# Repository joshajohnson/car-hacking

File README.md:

# Car Hacking

A repo for assorted tools, projects, and documentation.

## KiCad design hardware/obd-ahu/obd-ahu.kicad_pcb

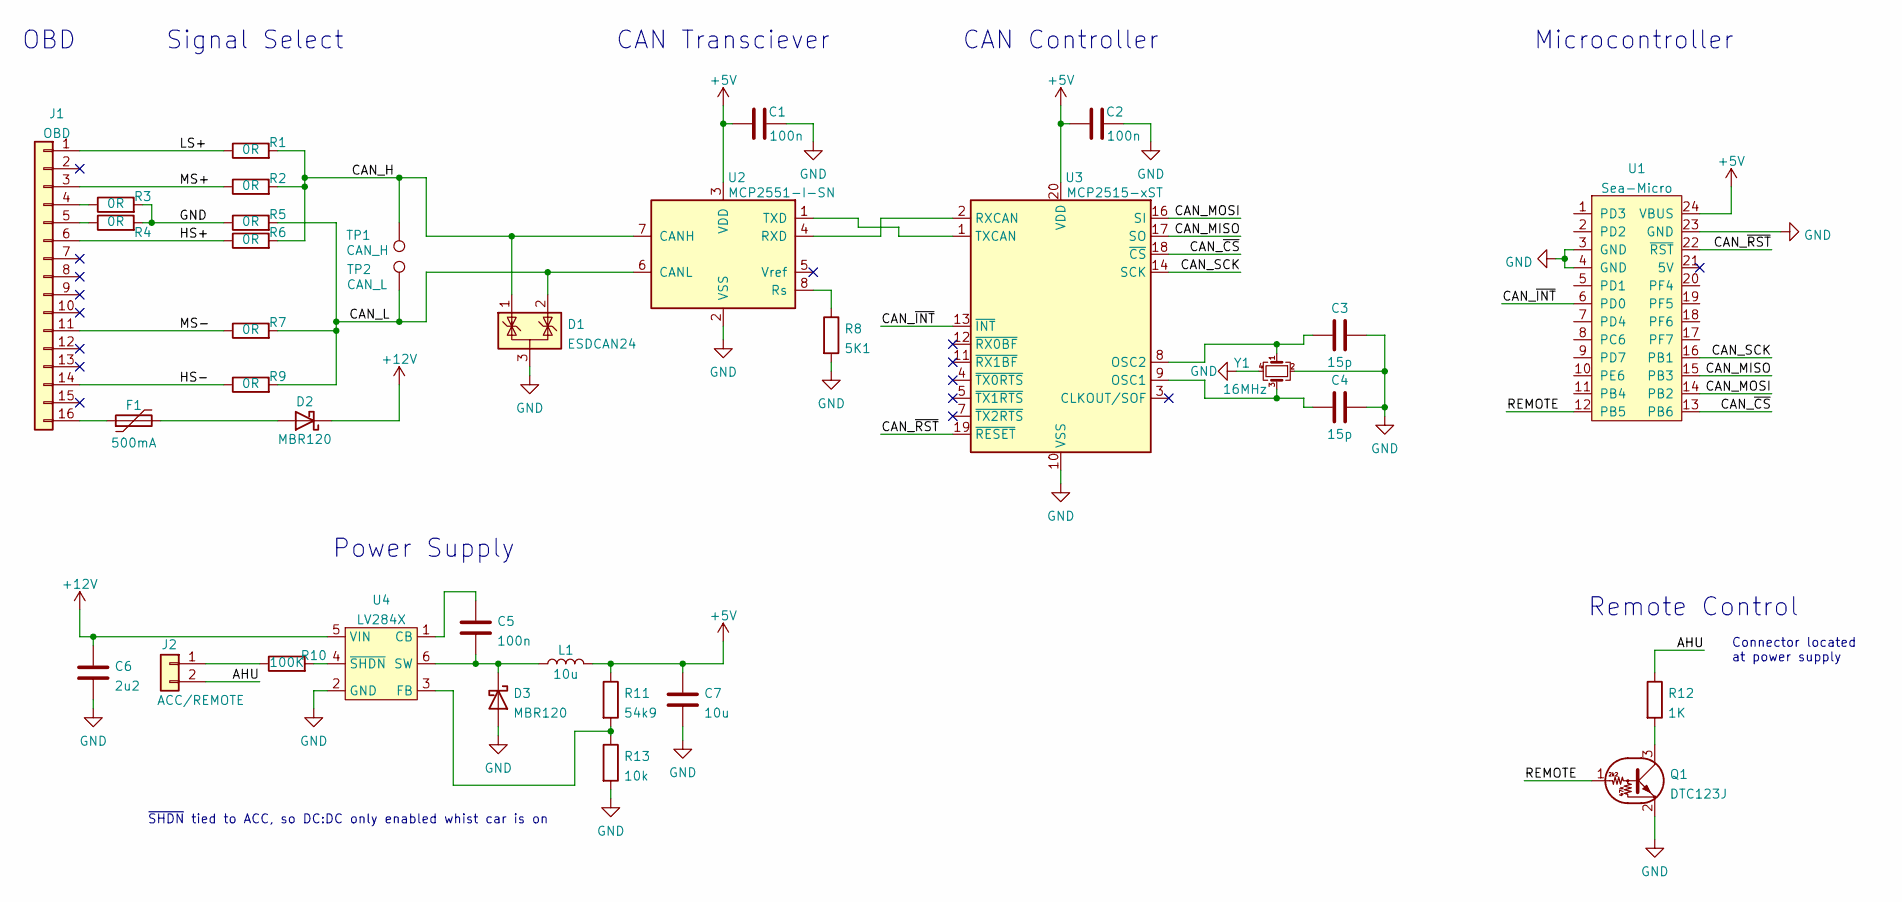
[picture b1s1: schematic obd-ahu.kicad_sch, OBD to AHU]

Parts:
C1, C2, C5: 100n; C_0603_1608Metric
C3, C4: 15p; C_0603_1608Metric; MPN CL10C150JB8NNNC; LCSC C1644
C6: 2u2; C_0805_2012Metric
C7: 10u; C_0805_2012Metric
D1: ESDCAN24; SOT-23
D2, D3: MBR120; D_SOD-123FL
F1: 500mA; Fuse_0805_2012Metric
J1: OBD; OBD-II-Sparkfun
J2: ACC/REMOTE; TerminalBlock_4Ucon_1x02_P3.50mm_Horizontal
L1: 10u; L_1210_3225Metric
Q1: DTC123J; TSOT-23
R1, R2, R5, R6, R7, R9: 0R; R_0603_1608Metric
R3, R4: 0R; R_0805_2012Metric
R8: 5K1; R_0603_1608Metric
R10: 100K; R_0603_1608Metric
R11: 54k9; R_0603_1608Metric
R12: 1K; R_0603_1608Metric
R13: 10k; R_0603_1608Metric
TP1: CAN_H; TestPoint_THTPad_D1.5mm_Drill0.7mm
TP2: CAN_L; TestPoint_THTPad_D1.5mm_Drill0.7mm
U1: Sea-Micro; Arduino_Pro_Micro
U2: MCP2551-I-SN; SOIC-8_3.9x4.9mm_P1.27mm
U3: MCP2515-xST; TSSOP-20_4.4x6.5mm_P0.65mm
U4: LV284X; TSOT-23-6
Y1: 16MHz; Crystal_SMD_3225-4Pin_3.2x2.5mm; MPN TAXM16M4RDBCCT2T; LCSC C164044

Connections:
+5V: C1.1, C2.1, C7.1, L1.2, R11.1, U1.24 (VBUS), U2.3 (VDD), U3.20 (VDD)
+12V: C6.1, D2.1 (K), U4.5 (VIN)
/AHU: J2.2, R12.1
/CAN_H: D1.1 (K), R1.2, R2.2, R6.2, TP1.1, U2.7 (CANH)
/CAN_L: D1.2 (K), R5.2, R7.2, R9.2, TP2.1, U2.6 (CANL)
/CAN_MISO: U1.15 (PB3), U3.17 (SO)
/CAN_MOSI: U1.14 (PB2), U3.16 (SI)
/CAN_SCK: U1.16 (PB1), U3.14 (SCK)
/CAN_~CS: U1.13 (PB6), U3.18 (~CS)
/CAN_~INT: U1.6 (PD0), U3.13 (~INT)
/CAN_~RST: U1.22 (~RST), U3.19 (~RESET)
/HS+: J1.6, R6.1
/HS-: J1.14, R9.1
/LS+: J1.1, R1.1
/MS+: J1.3, R2.1
/MS-: J1.11, R7.1
/REMOTE: Q1.1 (B), U1.12 (PB5)
GND: C1.2, C2.2, C3.2, C4.2, C6.2, C7.2, D1.3 (A), D3.2 (A), Q1.2 (E), R3.2, R4.2, R5.1, R8.2, R13.2, U1.3 (GND), U1.4 (GND), U1.23 (GND), U2.2 (VSS), U3.10 (VSS), U4.2 (GND), Y1.2, Y1.4
unnamed: C3.1, U3.8 (OSC2), Y1.1
unnamed: C4.1, U3.9 (OSC1), Y1.3
unnamed: C5.1, U4.1 (CB)
unnamed: C5.2, D3.1 (K), L1.1, U4.6 (SW)
unnamed: D2.2 (A), F1.2
unnamed: F1.1, J1.16
unnamed: J1.4, R3.1
unnamed: J1.5, R4.1
unnamed: Q1.3 (C), R12.2
unnamed: R8.1, U2.8 (Rs)
unnamed: J2.1, R10.1
unnamed: R10.2, U4.4 (~SHDN)
unnamed: R11.2, R13.1, U4.3 (FB)
unnamed: U2.1 (TXD), U3.1 (TXCAN)
unnamed: U2.4 (RXD), U3.2 (RXCAN)

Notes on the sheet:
OBD
~{SHDN} tied to ACC, so DC:DC only enabled whist car is on
Signal Select
Power Supply
CAN Transciever
CAN Controller
Microcontroller
Remote Control
Connector located at power supply

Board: 2 copper layers, 35 parts (35 on the bottom side), 33 nets, no tracks yet.

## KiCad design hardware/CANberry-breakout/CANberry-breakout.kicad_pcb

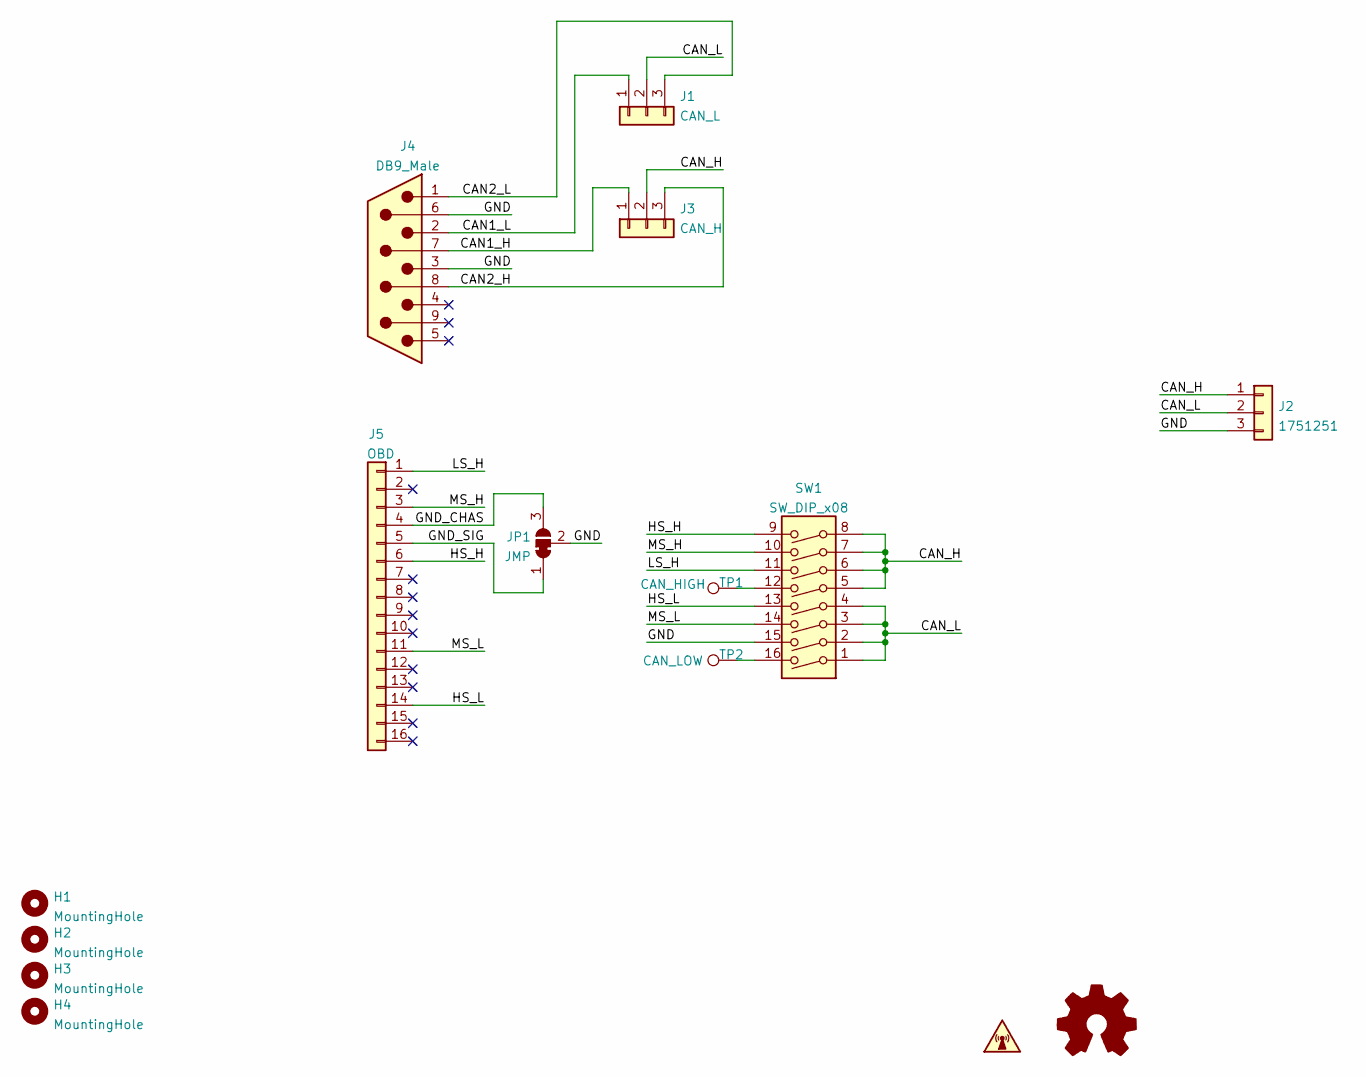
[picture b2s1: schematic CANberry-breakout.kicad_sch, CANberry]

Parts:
H1, H2, H3, H4: MountingHole; MountingHole_3.2mm_M3
J1: CAN_L; 3_PIN_THT_Staggered
J2: 1751251; TerminalBlock_393570003_1x03_P3.50mm_Horizontal; MPN 1751251; LCSC C91152
J3: CAN_H; 3_PIN_THT_Staggered
J4: DB9_Male; DSUB-9_Male_Horizontal_P2.77x2.84mm_EdgePinOffset7.70mm_Hou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
J5: OBD; OBD-II-Sparkfun
JP1: JMP; SolderJumper-3_P1.3mm_Bridged12_RoundedPad1.0x1.5mm
LOGO1: Logo_Open_Hardware_Small; OSHW-Symbol_8.9x8mm_Copper
SW1: SW_DIP_x08; SW_DIP_SPSTx08_Slide_9.78x22.5mm_W7.62mm_P2.54mm
SYM1: Canberry
TP1: CAN_HIGH; TestPoint_THTPad_D2.0mm_Drill1.0mm
TP2: CAN_LOW; TestPoint_THTPad_D2.0mm_Drill1.0mm

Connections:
/CAN1_H: J3.1, J4.7
/CAN1_L: J1.1, J4.2
/CAN2_H: J3.3, J4.8
/CAN2_L: J1.3, J4.1
/CAN_H: J2.1, J3.2, SW1.5, SW1.6, SW1.7, SW1.8
/CAN_L: J1.2, J2.2, SW1.1, SW1.2, SW1.3, SW1.4
/GND: J2.3, J4.3, J4.6, JP1.2 (C), SW1.15
/GND_CHAS: J5.4, JP1.3 (B)
/GND_SIG: J5.5, JP1.1 (A)
/HS_H: J5.6, SW1.9
/HS_L: J5.14, SW1.13
/LS_H: J5.1, SW1.11
/MS_H: J5.3, SW1.10
/MS_L: J5.11, SW1.14
unnamed: SW1.12, TP1.1
unnamed: SW1.16, TP2.1

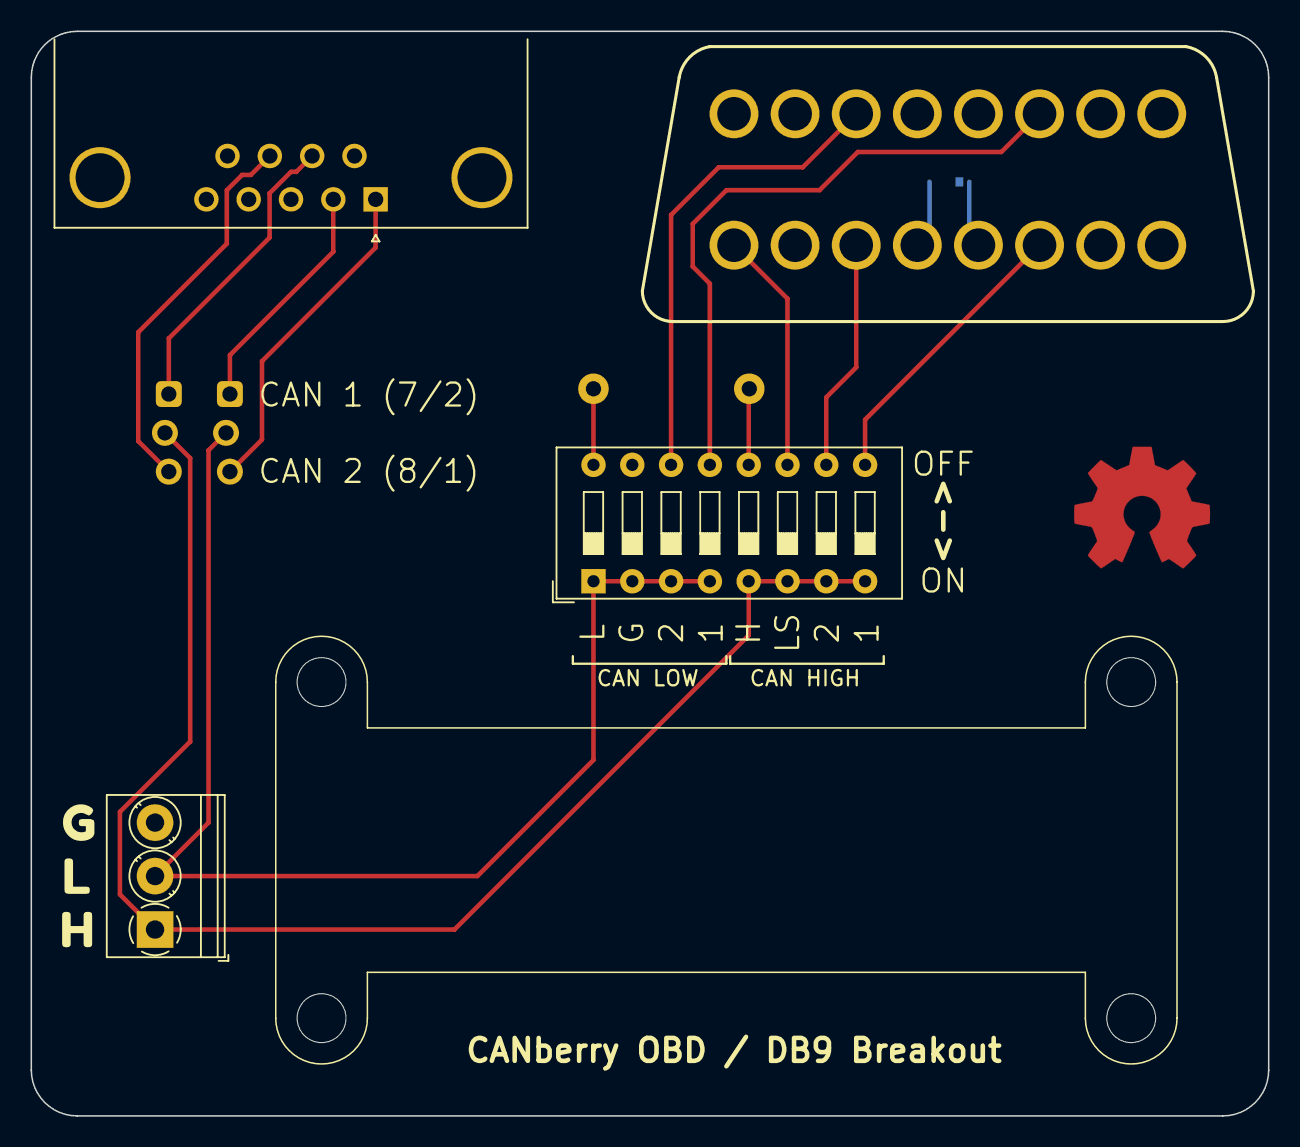
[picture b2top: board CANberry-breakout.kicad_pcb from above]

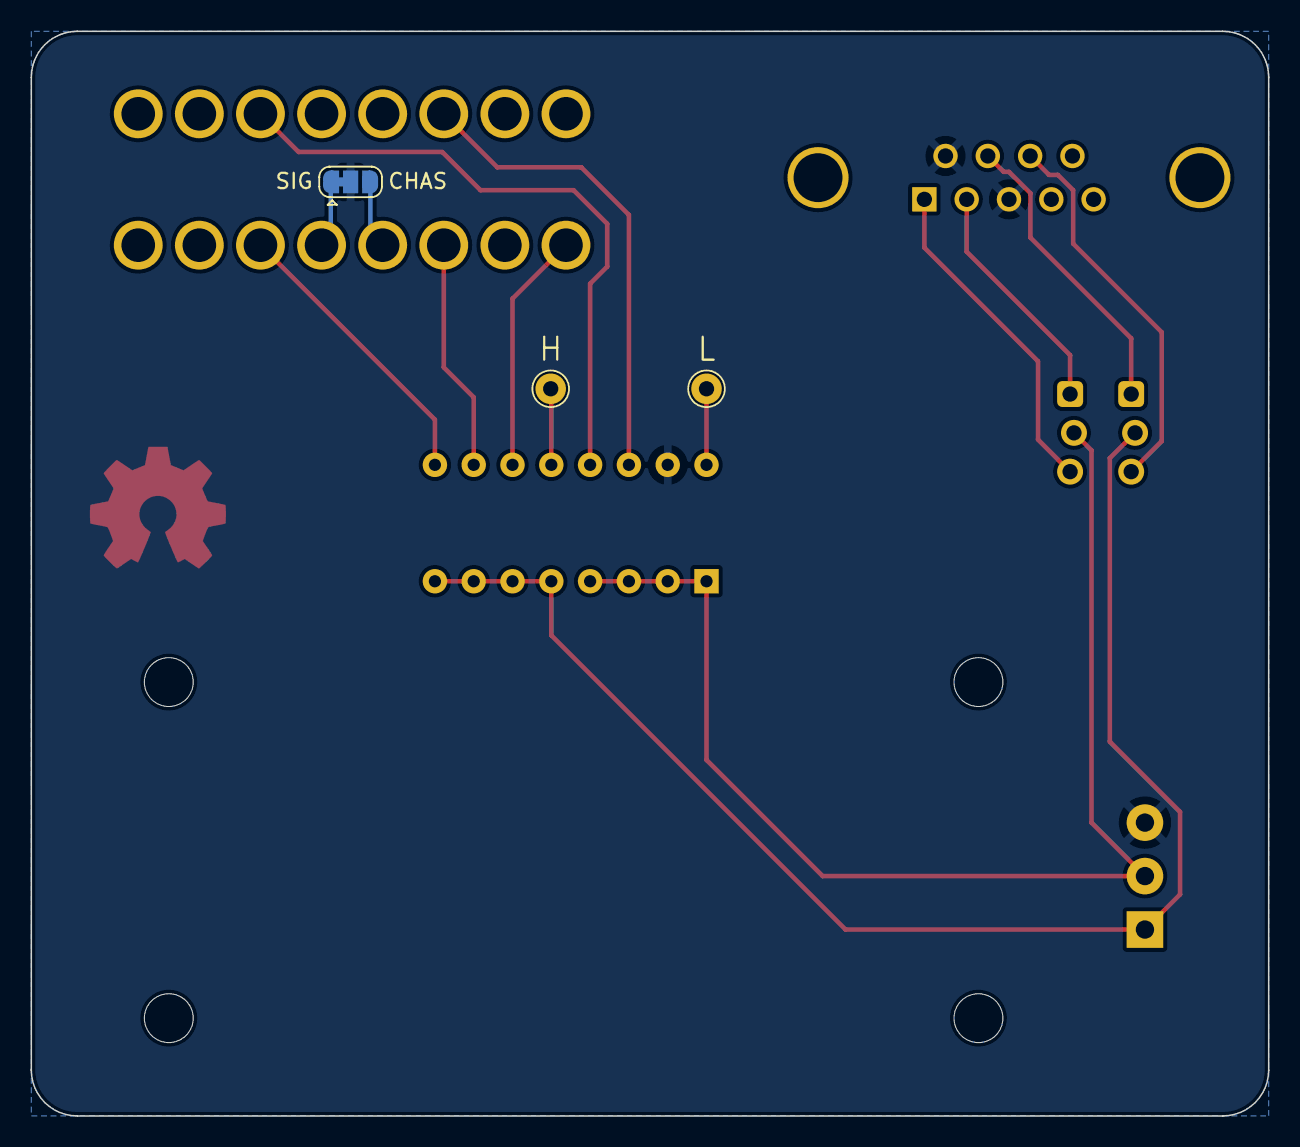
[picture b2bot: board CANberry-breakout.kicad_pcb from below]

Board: 2 copper layers, 81.0 x 71.0 mm, 18 parts (3 on the bottom side), 16 nets.

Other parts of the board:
svg2mod, svg2mod#2, svg2mod#3: G***; svg2mod

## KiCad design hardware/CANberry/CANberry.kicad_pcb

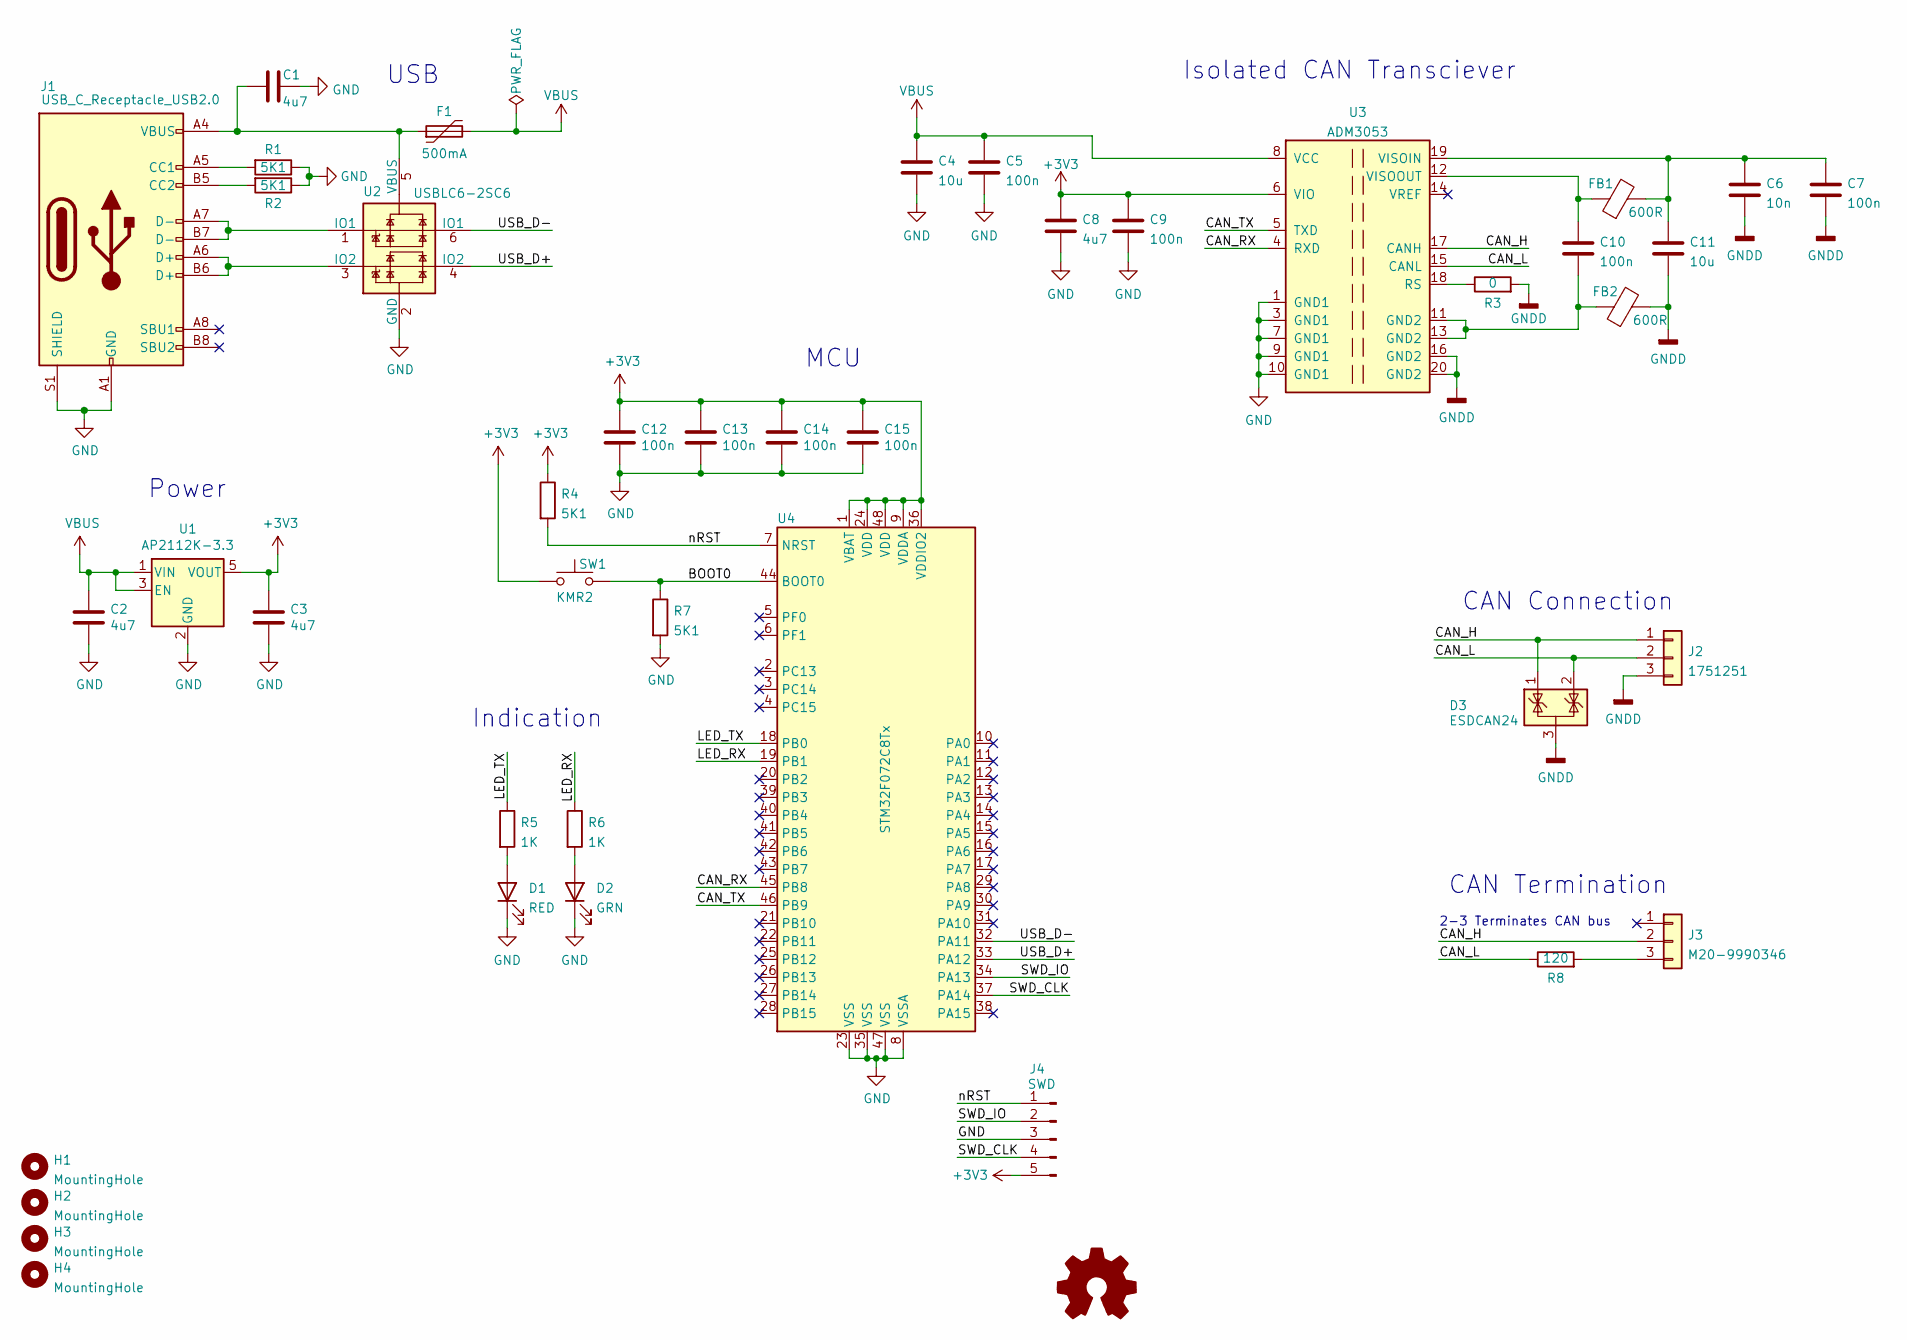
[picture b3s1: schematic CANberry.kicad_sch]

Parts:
C1, C8: 4u7; C_0603_1608Metric
C2, C3: 4u7; C_0603_1608Metric; DigiKey 1276-1866-1-ND
C4, C11: 10u; C_0805_2012Metric; MPN GRM21BR61E106KA73L; LCSC C84416
C5, C7, C9, C10: 100n; C_0603_1608Metric
C6: 10n; C_0603_1608Metric
C12, C13, C14, C15: 100n; C_0603_1608Metric; DigiKey 1276-1000-1-ND
D1: RED; LED_0603_1608Metric
D2: GRN; LED_0603_1608Metric
D3: ESDCAN24; SOT-23; MPN ESDCAN24-2BLY; LCSC C970030
F1: 500mA; Fuse_0603_1608Metric
FB1, FB2: 600R; Ferrite_Bead_0603
H1, H2, H3, H4: MountingHole; MountingHole_3.2mm_M3
J1: USB_C_Receptacle_USB2.0; USB_C_Receptacle_HRO_TYPE-C-31-M-12; MPN TYPE-C-31-M-14; LCSC C223907
J2: 1751251; TerminalBlock_393570003_1x03_P3.50mm_Horizontal; MPN 1751251; LCSC C91152
J3: M20-9990346; 3_PIN_THT_Staggered
J4: SWD; 5_PIN_SMD_PROG
LOGO1: Logo_Open_Hardware_Small; OSHW_Logo_3.6x3.6_F.Mask
R1, R2, R4, R7: 5K1; R_0603_1608Metric
R3: 0; R_0603_1608Metric
R5, R6: 1K; R_0603_1608Metric
R8: 120; R_0603_1608Metric
SW1: KMR2; SW_Push_KMR2; MPN KMR221GLFS; LCSC C72443
U1: AP2112K-3.3; SOT-23-5; MPN AP2112K-3.3TRG1; LCSC C51118
U2: USBLC6-2SC6; SOT-23-6; MPN USBLC6-2SC6; LCSC C7519
U3: ADM3053; SOIC-20W_7.5x12.8mm_P1.27mm; MPN ADM3053; LCSC C117821
U4: STM32F072C8Tx; LQFP-48_7x7mm_P0.5mm; MPN STM32F072C8T6; LCSC C80488

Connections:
+3V3: C3.2, C8.1, C9.1, C12.1, C13.1, C14.1, C15.1, J4.5, R4.1, SW1.1, U1.5 (VOUT), U3.6 (VIO), U4.1 (VBAT), U4.9 (VDDA), U4.24 (VDD), U4.36 (VDDIO2), U4.48 (VDD)
/BOOT0: R7.1, SW1.2, U4.44 (BOOT0)
/CAN_H: D3.1 (K), J2.1, J3.2, U3.17 (CANH)
/CAN_L: D3.2 (K), J2.2, R8.1, U3.15 (CANL)
/CAN_RX: U3.4 (RXD), U4.45 (PB8)
/CAN_TX: U3.5 (TXD), U4.46 (PB9)
/LED_RX: R6.1, U4.19 (PB1)
/LED_TX: R5.1, U4.18 (PB0)
/SWD_CLK: J4.4, U4.37 (PA14)
/SWD_IO: J4.2, U4.34 (PA13)
/USB_D+: U2.4 (IO2), U4.33 (PA12)
/USB_D-: U2.6 (IO1), U4.32 (PA11)
/nRST: J4.1, R4.2, U4.7 (NRST)
GND: C1.2, C2.1, C3.1, C4.2, C5.2, C8.2, C9.2, C12.2, C13.2, C14.2, C15.2, D1.1 (K), D2.1 (K), J1.A1 (GND), J1.A12 (GND), J1.B1 (GND), J1.B12 (GND), J1.S1 (SHIELD), J4.3, R1.1, R2.1, R7.2, U1.2 (GND), U2.2 (GND), U3.1 (GND1), U3.3 (GND1), U3.7 (GND1), U3.9 (GND1), U3.10 (GND1), U4.8 (VSSA), U4.23 (VSS), U4.35 (VSS), U4.47 (VSS)
GNDD: C6.2, C7.2, C11.2, D3.3 (A), FB2.2, J2.3, R3.2, U3.16 (GND2), U3.20 (GND2)
unnamed: C1.1, F1.1, J1.A4 (VBUS), J1.A9 (VBUS), J1.B4 (VBUS), J1.B9 (VBUS), U2.5 (VBUS)
unnamed: C10.1, FB1.1, U3.12 (VISOOUT)
unnamed: C10.2, FB2.1, U3.11 (GND2), U3.13 (GND2)
unnamed: C6.1, C7.1, C11.1, FB1.2, U3.19 (VISOIN)
unnamed: D1.2 (A), R5.2
unnamed: D2.2 (A), R6.2
unnamed: J1.A5 (CC1), R1.2
unnamed: J1.A6 (D+), J1.B6 (D+), U2.3 (IO2)
unnamed: J1.A7 (D-), J1.B7 (D-), U2.1 (IO1)
unnamed: J1.B5 (CC2), R2.2
unnamed: J3.3, R8.2
unnamed: R3.1, U3.18 (RS)
VBUS: C2.2, C4.1, C5.1, F1.2, U1.1 (VIN), U1.3 (EN), U3.8 (VCC)

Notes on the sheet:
Power
USB
Indication
MCU
Isolated CAN Transciever
2-3 Terminates CAN bus
CAN Termination
CAN Connection

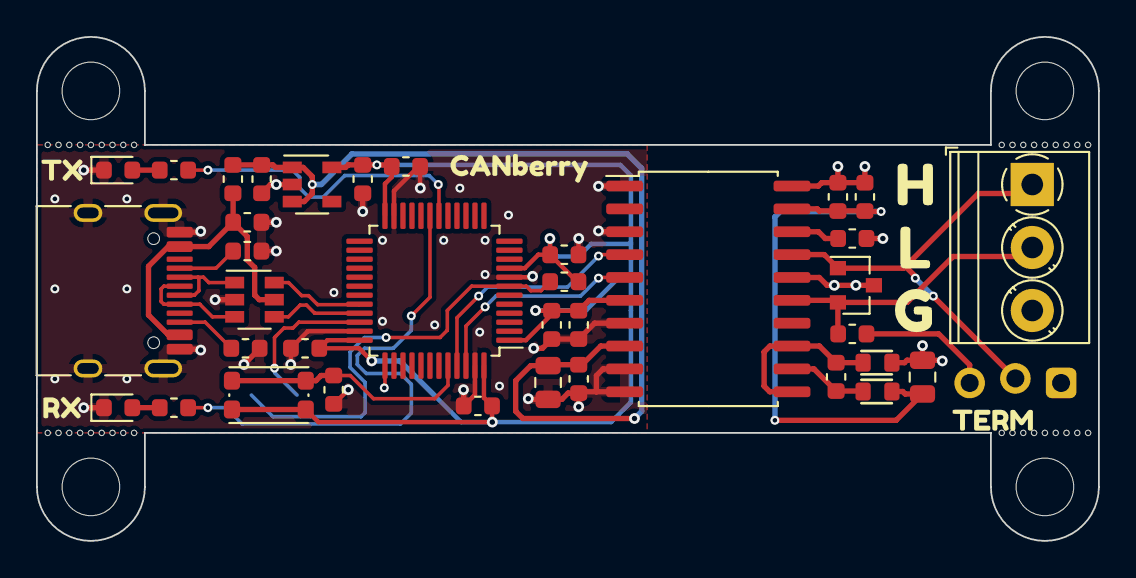
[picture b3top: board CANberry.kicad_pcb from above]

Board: 2 copper layers, 59.0 x 28.0 mm, 50 parts (1 on the bottom side), 28 nets.

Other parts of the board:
svg2mod, svg2mod#2, svg2mod#3, svg2mod#4, svg2mod#5, svg2mod#6, svg2mod#7: G***; svg2mod

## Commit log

2021-09-26 cancat laid out
2021-10-02 rename to CANberry due to name colision
2021-10-10 tidy up canberry, add obd/db9 breakout
2021-10-15 add obd ahu schematic
2021-12-31 add obd ahu firmware
